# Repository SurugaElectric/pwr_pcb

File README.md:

<a href="https://github.com/SurugaElectric/pwr_pcb">SurugaElec. Power supply board</a> © 2025 by <a href="https://github.com/SurugaElectric">SurugaElectric</a> is licensed under <a href="https://creativecommons.org/licenses/by-sa/4.0/">CC BY-SA 4.0</a>

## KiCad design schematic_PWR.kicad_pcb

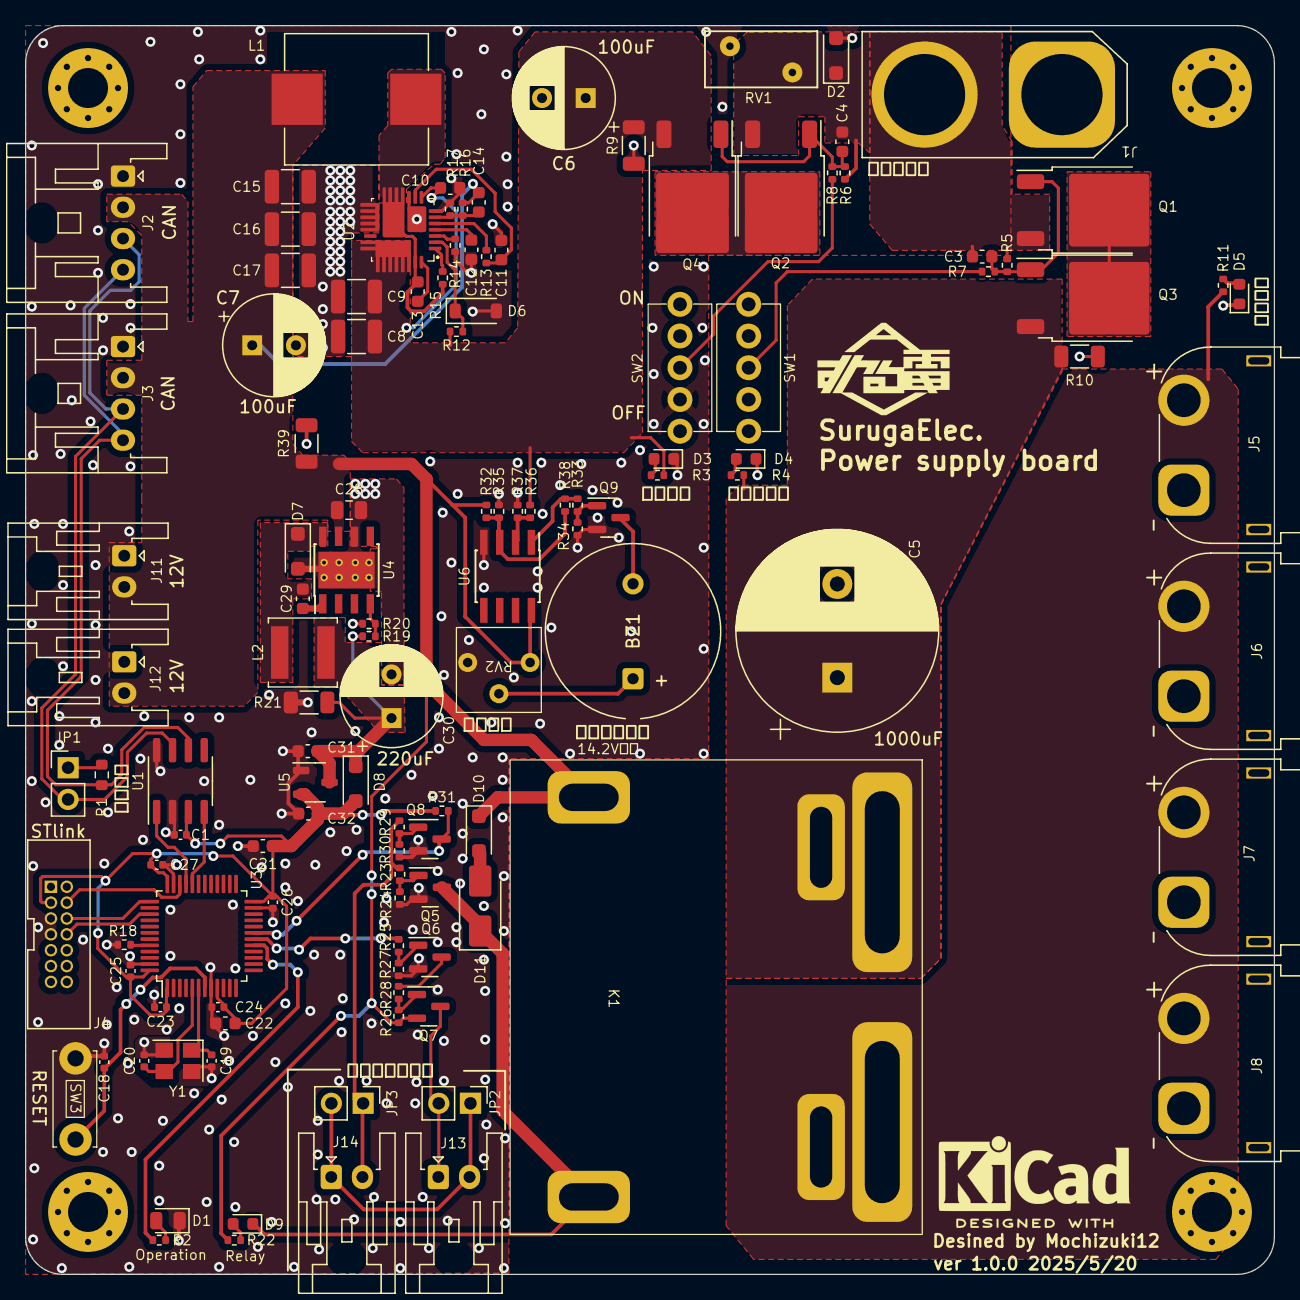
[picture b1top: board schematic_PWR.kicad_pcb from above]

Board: 2 copper layers, 100.0 x 100.0 mm, 125 parts (0 on the bottom side), 62 nets.

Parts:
BZ1: Buzzer; Indicator_PUI_AI-1440-TWT-24V-2-R
C1, C18, C23, C24, C25, C26, C27: 0.1uF; C_0402_1005Metric
C3, C4, C10: 0.1uF; C_0603_1608Metric
C5: 1000uF; CP_Radial_D16.0mm_P7.50mm
C6, C7: 100uF; CP_Radial_D8.0mm_P3.50mm
C8, C9: 10uF; C_1210_3225Metric
C11: 4.7uF; C_0603_1608Metric
C12: 47nF; C_0603_1608Metric
C13, C31, C32: 1uF; C_0603_1608Metric
C14: 68p; C_0603_1608Metric
C15, C16, C17: 47uF; C_1210_3225Metric
C19, C20: 15pF; C_0402_1005Metric
C21, C22: 10uF; C_0603_1608Metric
C28: 10uF; C_0805_2012Metric
C29: 0.01uF; C_0603_1608Metric
C30: 220uF; CP_Radial_D8.0mm_P3.50mm
D1: LED; LED_0805_2012Metric
D2, D7, D8: D_Schottky; D_SOD-123F
D3, D4, D5, D9: LED; LED_0603_1608Metric
D6: D_Zener; D_SOD-123
D10: D; D_SOD-123F
D11: D_Zener; D_SMA
H1, H2, H3, H4: MountingHole_Pad; MountingHole_3.2mm_M3_Pad_Via
J1: Conn_01x02; XT90-M
J2, J3: Conn_01x04; JST_XA_S04B-XASK-1_1x04_P2.50mm_Horizontal
J4: STlink_v3; JTAG_box_connector
J5, J6, J7, J8: Conn_01x02; AMASS_XT60PW-F_1x02_P7.20mm_Horizontal
J11, J12, J13, J14: Conn_01x02; JST_XA_S02B-XASK-1_1x02_P2.50mm_Horizontal
JP1, JP2, JP3: Jumper; PinHeader_1x02_P2.54mm_Vertical
K1: HE1AN-W-DC12V-Y6; HE1AN-W-DC12V-Y6+Y5
L1: 8.2uH; L_Sunlord_MWSA1004S
L2: 15uH; L_Sunlord_SWPA5040S
Q1, Q2, Q3, Q4: Q_PMOS_GSD; TO-252-2
Q5, Q6, Q8, Q9: Q_NMOS_GSD; SOT-23
Q7: Q_PMOS_GSD; SOT-23
R1: 120; R_0603_1608Metric
R2: 1.2k; R_0402_1005Metric
R3, R4, R5, R6, R7, R8, R11, R12, R13, R18, R22, R24, R26, R27, R28, R30, R31, R34, R35: 10k; R_0402_1005Metric
R9, R10, R21, R39: 10k; R_1206_3216Metric
R14: 205k; R_0402_1005Metric
R15: 4.7k; R_0402_1005Metric
R16: 47k; R_0402_1005Metric
R17, R32: 2.4k; R_0402_1005Metric
R19, R36: 12k; R_0402_1005Metric
R20: 3.9k; R_0402_1005Metric
R23, R25, R29, R33: 100; R_0402_1005Metric
R37: 20k; R_0402_1005Metric
R38: 15k; R_0402_1005Metric
RV1: Varistor; RV_Disc_D9mm_W4.5mm_P5mm
RV2: 10k; GF063P
SW1, SW2: SW_SPST; Toggle_switch
SW3: SW_SPST; TVBP06-B043
U1: SN65HVD230; SOIC-8_3.9x4.9mm_P1.27mm
U2: XR76208
U3: STM32F103CBTx; LQFP-48_7x7mm_P0.5mm
U4: TPS5430DDA; TI_SO-PowerPAD-8_ThermalVias
U5: XC6206P332MR-G; SOT-23-3
U6: LM393; PowerIntegrations_SO-8
Y1: 12MHz; Crystal_SMD_3225-4Pin_3.2x2.5mm

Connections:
+3.3V: C1.2, C21.1, C22.1, C23.1, C24.1, C25.1, C26.1, C27.1, C32.1, D8.2 (A), J4.3, R31.1, U1.3 (VCC), U3.1 (VBAT), U3.9 (VDDA), U3.24 (VDD), U3.36 (VDD), U3.48 (VDD), U5.2 (VO)
+5V: C30.1, C31.1, D8.1 (K), L2.2, R19.1, R21.1, U5.3 (VI)
+12V: C7.1, C14.1, C15.1, C16.1, C17.1, C28.1, D10.1 (K), J2.2, J3.2, J11.2, J12.2, K1.4, L1.2, Q7.2 (S), R16.1, R22.1, R26.1, R32.1, R39.1, RV2.1, U4.7 (VIN), U6.8 (V+)
+BATT: C3.1, C4.1, D2.1 (K), J1.2, Q1.3 (S), Q2.3 (S), R5.1, R6.1, RV1.1
/EMS/MCU_EMC_signal: R25.2, U3.18 (PB0)
/EMS/MCU_EMS_Observe: Q8.3 (D), R31.2, U3.19 (PB1)
/EMS/Relay_Signal_OUT: J14.2, JP3.1 (A), R23.1, R29.2
/Power_relay/Main_power_OUT: J5.2, J6.2, J7.2, J8.2, K1.2, R11.1
/STM32F103/CAN_RX: U1.4 (R), U3.32 (PA11)
/STM32F103/CAN_TX: U1.1 (D), U3.33 (PA12)
/STM32F103/SWCLK: J4.6, U3.37 (PA14)
/STM32F103/SWDIO: J4.4, U3.34 (PA13)
/STM32F103/SWO: J4.8, U3.39 (PB3)
Actuator_Power: C5.1, K1.1, Q3.3 (S), R4.1, R10.1
GND: C1.1, C5.2, C6.2, C7.2, C8.2, C9.2, C10.2, C11.2, C12.2, C15.2, C16.2, C17.2, C18.2, C19.2, C20.2, C21.2, C22.2, C23.2, C24.2, C25.2, C26.2, C27.2, C28.2, C30.2, C31.2, C32.2, D1.1 (K), D2.2 (A), D3.1 (K), D4.1 (K), D5.1 (K), D6.2 (A), D7.2 (A), J1.1, J2.1, J3.1, J4.5, J4.7, J5.1, J6.1, J7.1, J8.1, J11.1, J12.1, Q5.2 (S), Q6.2 (S), Q8.2 (S), Q9.2 (S), R9.2, R10.2, R14.2, R17.2, R18.2, R20.2, R21.2, R24.2, R27.2, R30.2, R34.1, R35.2, R37.2, R39.2, RV1.2, RV2.3, SW1.1 (A), SW2.1 (A), SW3.1 (A), U1.2 (GND), U1.8 (Rs), U2.7 (AGND), U2.10 (AGND), U2.15 (PGND), U2.16 (PGND), U2.17 (PGND), U2.18 (PGND), U2.19 (PGND), U2.AGND, U2.PGND, U3.8 (VSSA), U3.23 (VSS), U3.35 (VSS), U3.47 (VSS), U4.6 (GND), U4.9 (GNDPAD), U5.1 (GND), U6.4 (V-), Y1.2, Y1.4
Logic_line_Power: C6.1, C8.1, C9.1, C10.1, Q4.3 (S), R3.1, R9.1, R12.1, R36.1, U2.8 (V_{IN}), U2.21 (P_{VIN}), U2.22 (P_{VIN}), U2.23 (P_{VIN}), U2.24 (P_{VIN}), U2.25 (P_{VIN}), U2.26 (P_{VIN}), U2.27 (P_{VIN}), U2.28 (P_{VIN}), U2.PVIN (P_{VIN})
MCU_running: R2.1, U3.17 (PA7)
unnamed: BZ1.2 (+), Q9.3 (D)
unnamed: BZ1.1 (-), RV2.2
unnamed: C13.1, L1.1, R15.1, U2.11 (SW), U2.12 (SW), U2.13 (SW), U2.14 (SW), U2.29 (SW), U2.SW
unnamed: D1.2 (A), R2.2
unnamed: D3.2 (A), R3.2
unnamed: D4.2 (A), R4.2
unnamed: D5.2 (A), R11.2
unnamed: D6.1 (K), R12.2, U2.2 (EN/MODE)
unnamed: C29.2, D7.1 (K), L2.1, U4.8 (PH)
unnamed: D9.2 (A), R22.2
unnamed: D10.2 (A), D11.2 (A)
unnamed: D9.1 (K), D11.1 (K), K1.3, Q5.3 (D)
unnamed: J2.3, J3.3, JP1.2 (B), U1.7 (CANH)
unnamed: J2.4, J3.4, R1.2, U1.6 (CANL)
unnamed: J13.1, JP2.2 (B), Q7.3 (D)
unnamed: J13.2, J14.1, JP2.1 (A), JP3.2 (B)
unnamed: JP1.1 (A), R1.1
unnamed: Q1.2 (D), Q3.2 (D)
unnamed: C3.2, Q1.1 (G), Q3.1 (G), R5.2, R7.1
unnamed: Q2.2 (D), Q4.2 (D)
unnamed: C4.2, Q2.1 (G), Q4.1 (G), R6.2, R8.1
unnamed: Q5.1 (G), R23.2, R24.1
unnamed: Q6.3 (D), R28.2
unnamed: Q6.1 (G), R25.1, R27.1
unnamed: Q7.1 (G), R26.2, R28.1
unnamed: Q8.1 (G), R29.1, R30.1
unnamed: Q9.1 (G), R33.1, R34.2
unnamed: R33.2, R38.1, U6.1
unnamed: R7.2, SW1.2 (B)
unnamed: R8.2, SW2.2 (B)
unnamed: C18.1, SW3.2 (B), U3.7 (NRST)
unnamed: C13.2, U2.30 (BST)
unnamed: C14.2, R16.2, R17.1, U2.6 (FB)
unnamed: R15.2, U2.1 (I_{LIM})
unnamed: R13.1, U2.5 (P_{GOOD})
unnamed: C12.1, U2.4 (SS)
unnamed: R14.1, U2.3 (T_{ON})
unnamed: C11.1, R13.2, U2.9 (V_{CC})
unnamed: R18.1, U3.44 (BOOT0)
unnamed: C20.1, U3.5 (PD0), Y1.3
unnamed: C19.1, U3.6 (PD1), Y1.1
unnamed: C29.1, U4.1 (BOOT)
unnamed: R19.2, R20.1, U4.4 (VSENSE)
unnamed: R32.2, R35.1, R38.2, U6.3 (+)
unnamed: R36.2, R37.1, U6.2 (-)

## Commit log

2025-05-20 v1.0.0
